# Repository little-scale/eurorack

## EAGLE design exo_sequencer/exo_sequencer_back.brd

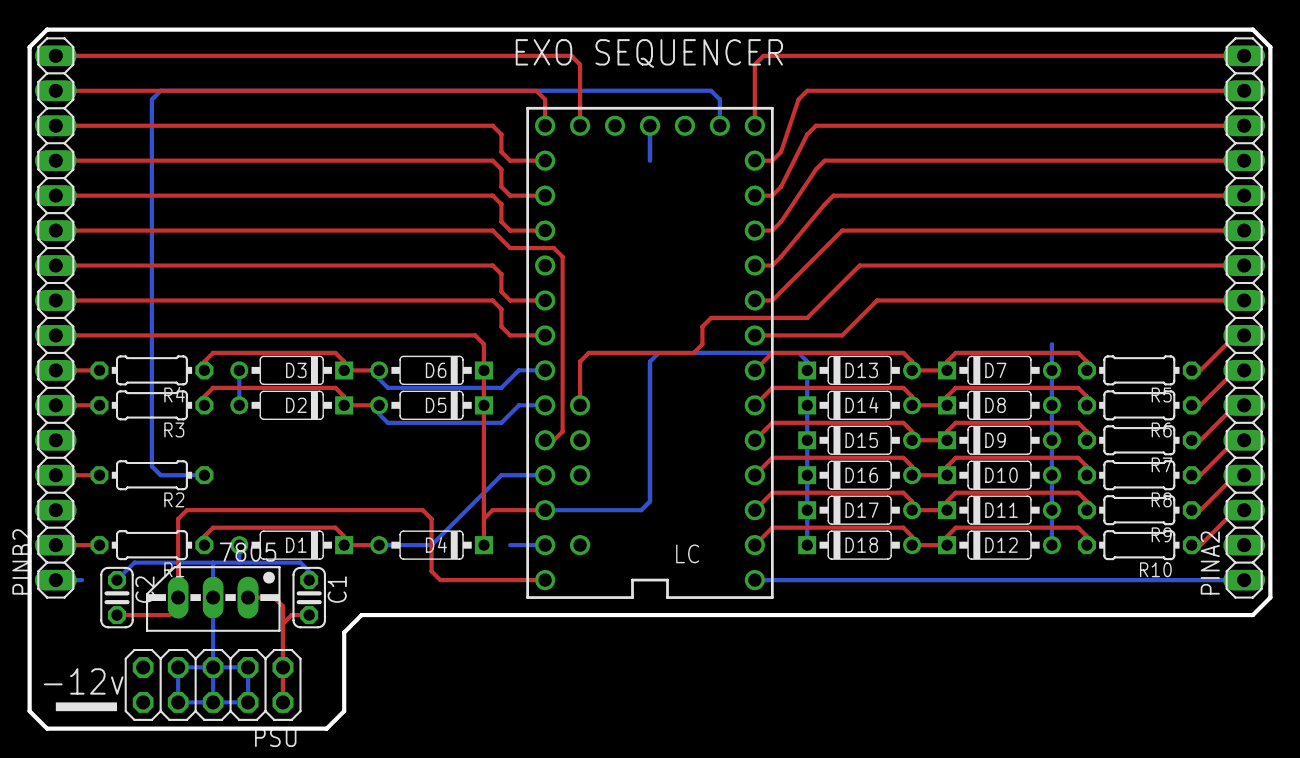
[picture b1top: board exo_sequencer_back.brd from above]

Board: 2 copper layers, 90.2 x 50.8 mm, 35 parts (0 on the bottom side), 38 nets.

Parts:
7805: 78MXXS
C1, C2: C025-024X044
D1, D2, D3, D4, D5, D6, D7, D8, D9, D10, D11, D12, D13, D14, D15, D16, D17, D18: DO35-7
LC: TEENSY_3.0-3.2&LC_ALL_PINS
PINA2: 1X16
PINB2: 1X16
PSU: 2X05
R1, R2, R3, R4, R5, R6, R7, R8, R9, R10: 0204/7

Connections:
3V: D4.C, D5.C, D6.C, D18.C, LC.3.3V, PINB2.8
G2: C1.1, C2.1, D1.A, D2.A, D3.A, D12.A, LC.AGND, LC.GND, LC.GND1, PINA2.1, PINB2.1, PSU.3, PSU.4, PSU.5, PSU.6, PSU.7, PSU.8
S$2: 7805.IN, C1.2
S$84: LC.14/A0, PINB2.14
S$85: LC.15/A1, PINB2.13
S$86: LC.19/A5, PINB2.9
S$87: LC.16/A2, PINB2.12
S$88: LC.22/A8, PINB2.11
S$89: LC.18/A4, PINB2.10
S$90: C2.2, LC.VIN
S$95: LC.8, PINA2.12
S$96: LC.7, PINA2.11
S$97: PINA2.3, R10.1
S$98: D10.C, D16.A, LC.2, R8.2
S$99: D9.C, D15.A, LC.3, R7.2
S$100: LC.RESET/DAC, PINB2.16
S$101: LC.13, PINB2.15
S$103: PINB2.7, R4.2
S$104: D3.C, D6.A, LC.20/A6, R4.1
S$106: D2.C, D5.A, LC.21/A7, R3.1
S$107: D1.C, D4.A, LC.23/A9, R1.1
S$109: LC.VBAT, R2.1
S$110: PINB2.4, R2.2
S$112: LC.12, PINA2.16
S$113: LC.11, PINA2.15
S$114: LC.10, PINA2.14
S$115: LC.9, PINA2.13
S$116: LC.6, PINA2.9
S$117: D7.C, D13.A, LC.5, R5.2
S$118: D11.C, D17.A, LC.1, R9.2
S$119: D8.C, D14.A, LC.4, R6.2
S$120: D12.C, D18.A, LC.0, R10.2
S$121: PINA2.4, R9.1
S$122: PINA2.5, R8.1
S$123: PINA2.6, R7.1
S$124: PINA2.7, R6.1
S$125: PINA2.8, R5.1
S$126: LC.A11, PINA2.10
